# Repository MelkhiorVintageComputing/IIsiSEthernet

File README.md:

# SEthernet for the Macintosh IIsi

This is a design for a PDS Ethernet device for the Macintosh IIsi & other macintoshes with a similar PDS slot. This is not my own design, but a redesign in a different form factor of [the SEthernet/30 for the Macintosh SE/30](https://github.com/rhalkyard/SEthernet). It's meant to be gateware- (for the CPLD), firmware- (the declaration ROM) and software-compatible (the Ethernet driver) with the original.

Known issues:
* The silkscreen for the slotid is backward between '0' and '1' (the slotid are negative logic)
* The Flash ROM is wired bit-reversed. While it has no impact on data or any regular software, it does cause an issue with the 'command bytes' from the ROM programmer - the 'command bytes' need to be bit-reversed to work, so this design is not compatible with the standard programRom.

License is the same as the original:

The hardware components of this project (board designs and programmable logic) are licensed under the Strongly-Reciprocal CERN Open Hardware License, version 2.

Please see also [the comments on licensing of the original design](https://github.com/rhalkyard/SEthernet?tab=readme-ov-file#license).

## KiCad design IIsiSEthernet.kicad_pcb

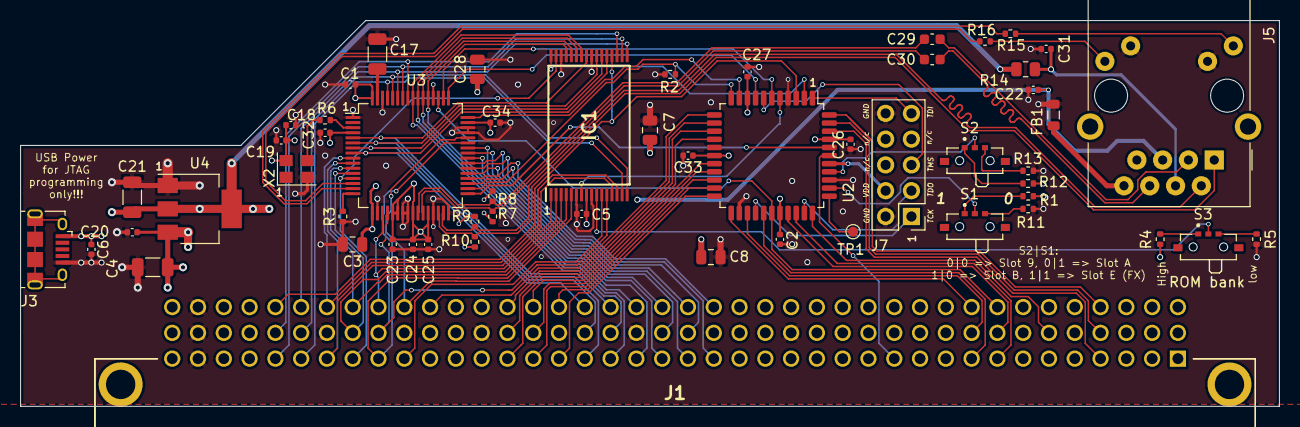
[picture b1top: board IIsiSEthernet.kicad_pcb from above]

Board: 4 copper layers, 124.0 x 38.0 mm, 56 parts (0 on the bottom side), 94 nets.

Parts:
C1, C2, C5, C6, C18, C20, C23, C24, C25, C26, C27, C32, C33, C34: 100nF 0402; C_0402_1005Metric
C3, C7, C8, C28: 1uF 0805; C_0805_2012Metric
C4, C17, C21: 10uF 1206; C_1206_3216Metric
C19, C22, C31: 10nF 0402; C_0402_1005Metric
C29, C30: 6.8nF 10% 0603; C_0603_1608Metric
FB1: Ferrite_Bead; L_0805_2012Metric
IC1: SST39SF010A-70-4C-WHE; SOP50P1400X120-32N
J1: 650906-5; 6509065
J3: USB_B_Micro; USB_Micro-B_Amphenol_10118194_Horizontal
J5: RJ45_Amphenol_RJMG1BD3B8K1ANR
J7: AVR-JTAG-10; PinHeader_2x05_P2.54mm_Vertical
R1, R4, R5, R11, R12, R13: 10k; R_0402_1005Metric
R2: 100k; R_0402_1005Metric
R3: 12.4k 1%; R_0402_1005Metric
R6: 33; R_0402_1005Metric
R7, R8, R9, R10: 49.9; R_0402_1005Metric
R14: 10 1/12W 1%; R_0805_2012Metric
R15, R16: 510 0402; R_0402_1005Metric
S1, S2, S3: SSAJ110100; SW_SSAJ110100
TP1: TestPoint; TestPoint_Pad_D1.0mm
U2: ATF1502ASL-25AU44; LQFP-44_10x10mm_P0.8mm
U3: ENC624J600-I_PT; TQFP-64_10x10mm_P0.5mm
U4: LD1117S33TR_SOT223; SOT-223-3_TabPin2
X2: ASE-xxxMHz; Oscillator_SMD_Abracon_ASE-4Pin_3.2x2.5mm

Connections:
+3V3: C1.1, C3.1, C18.1, C19.1, C21.1, C23.1, C24.1, C25.1, C28.1, C32.1, C34.1, R9.2, R10.2, R14.1, U3.4, U3.17, U3.21, U3.22, U3.25, U3.28, U3.47, U3.52, U3.64, U4.2, X2.4
+5V: C2.1, C4.1, C5.1, C6.1, C7.1, C8.1, C20.1, C26.1, C27.1, C33.1, IC1.8, J1.A37, J1.B13, J1.B19, J1.B25, J1.B31, J1.B37, J1.C37, J3.1, R1.2, R4.2, R12.2, U2.9, U2.17, U2.29, U2.41, U4.3
/Ethernet/RBIAS: R3.1, U3.16
/Ethernet/TP34: TP1.1, U2.34
/Ethernet/VCAP: C17.1, U3.63
/eth_conn/ETH_3V3: C31.1, J5.R4, R14.2
/eth_conn/RCT: C22.2, J5.R5, R7.2, R8.2
/eth_conn/RD+: C29.1, J5.R3
/eth_conn/RD-: C30.1, J5.R6
A0: IC1.20, J1.C36, U2.3
A1: IC1.19, J1.B36, U3.57
A2: IC1.18, J1.A36, U3.58
A3: IC1.17, J1.C35, U3.59
A4: IC1.16, J1.B35, U3.60
A5: IC1.15, J1.A35, U3.61
A6: IC1.14, J1.C34, U3.9
A7: IC1.13, J1.A34, U3.10
A8: IC1.3, J1.C33, U3.11
A9: IC1.2, J1.B33, U3.12
A10: IC1.31, J1.A33, U3.13
A11: IC1.1, J1.C32, U3.19
A12: IC1.12, J1.B32, U3.20
A13: IC1.4, J1.A32, U3.43
A14: IC1.5, J1.C31, U3.44
A15: IC1.11, J1.A31
A16: J1.C30, U2.12
A24: J1.C27, U2.13
A25: J1.B27, U2.14
A26: J1.A27, U2.15
A27: J1.C26, U2.18
A28: J1.B26, U2.19
A29: J1.A26, U2.20
A30: J1.C25, U2.21
A31: J1.A25, U2.22
CLK_25_000: R6.1, U3.3
D16: J1.A19, U3.35
D17: J1.C19, U3.36
D18: J1.A20, U3.37
D19: J1.B20, U3.38
D20: J1.C20, U3.39
D21: J1.A21, U3.40
D22: J1.B21, U3.41
D23: J1.C21, U3.42
D24: IC1.29, J1.A22, U3.53
D25: IC1.28, J1.C22, U3.54
D26: IC1.27, J1.A23, U3.55
D27: IC1.26, J1.B23, U3.56
D28: IC1.25, J1.C23, U3.5
D29: IC1.23, J1.A24, U3.6
D30: IC1.22, J1.B24, U3.7
D31: IC1.21, J1.C24, U3.8
ETH_B0SEL: U2.6, U3.50
ETH_B1SEL: U2.10, U3.48
ETH_CLKOUT: U2.40, U3.33
ETH_CS: U2.8, U3.49
ETH_~INT: R2.1, U2.11, U3.34
Earth: FB1.1, J5.R8
GND: C1.2, C2.2, C3.2, C4.2, C5.2, C6.2, C7.2, C8.2, C17.2, C18.2, C19.2, C20.2, C21.2, C22.1, C23.2, C24.2, C25.2, C26.2, C27.2, C28.2, C31.2, C32.2, C33.2, C34.2, FB1.2, IC1.6, IC1.9, IC1.24, IC1.30, J1.A39, J1.B16, J1.B22, J1.B28, J1.B34, J1.B39, J1.C39, J3.5, J5.L2, J5.L3, J7.2, J7.10, R2.2, R3.2, R5.2, R11.2, R13.2, U2.4, U2.16, U2.24, U2.36, U3.1, U3.18, U3.23, U3.24, U3.29, U3.32, U3.45, U3.46, U3.62, U4.1, X2.2
JTAG_TCK: J7.1, U2.26
JTAG_TDI: J7.9, U2.1
JTAG_TDO: J7.3, U2.32
JTAG_TMS: J7.5, U2.7
JTAG_VDD: J7.4, U2.38
LEDA: R15.2, U3.15
LEDB: R16.2, U3.14
unnamed: J5.L1, R16.1
unnamed: J5.L4, R15.1
unnamed: R1.1, S1.1
unnamed: R4.1, S3.1
unnamed: R5.1, S3.2
unnamed: R6.2, X2.3
unnamed: R11.1, S1.2
unnamed: R12.1, S2.1
unnamed: R13.1, S2.2
ROM_BANK: IC1.10, S3.C
SIZ0: J1.B9, U2.25
SIZ1: J1.A9, U2.27
TPIN+: C29.2, R8.1, U3.26
TPIN-: C30.2, R7.1, U3.27
TPOUT+: J5.R1, R10.1, U3.30
TPOUT-: J5.R2, R9.1, U3.31
~AS: J1.C9, U2.23
~DS: J1.B6, U2.33
~DSACK0: J1.B8, U2.30
~DSACK1: J1.A8, U2.31
~IRQ1: J1.C4, U2.44
~IRQ2: J1.B4, U2.43
~IRQ3: J1.A4, U2.42
~RESET: J1.A12, U2.39
~ROM_OE: IC1.32, U2.2
~ROM_WE: IC1.7, U2.5
~RW: J1.C8, U2.28, U3.51
~SLOTID_0: S1.C, U2.35
~SLOTID_1: S2.C, U2.37

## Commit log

2024-04-06 initial import
2024-04-07 minor stuff
2024-04-13 cleanups, switch for ROM bank
2024-04-14 silk cleanup
2024-04-14 27->33 ohms (basic...)
2024-05-02 link to original licensing terms
